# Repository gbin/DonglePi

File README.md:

DonglePi is a device that gives you a Raspberry Pi P1 compatible connector for your PC.

The RPi P1 is a defacto standard connector on all models with pins for:
- GPIO
- I2C
- SPI
- Serial
- PWM

[More info about it.](http://elinux.org/RPi_Low-level_peripherals)

On the software side, it exposes APIs that are compatible with the ones you can use on the Raspberry Pi like [GPIO](https://pypi.python.org/pypi/RPi.GPIO/) and [smbus](http://www.raspberry-projects.com/pi/programming-in-python/i2c-programming-in-python/using-the-i2c-interface-2) under python.

## Why ?

With DonglePi:
- you can use your familiar PC or Mac to directly develop & debug your RPi embedded applications (with an IDE for example)
- you can use peripherals made for the Raspberry Pi ecosystem on your PC. You can find a list of those [here](http://elinux.org/RPi_VerifiedPeripherals).

DonglePi can also be used to easily setup students for an embedded development course in a preexisting computer lab.

The fidelity with the original hardware won't be 100% but it doesn't need to be to be useful.

## Current Status

It is a prototype working on a breadboard.
The goal is to make a PCB like the one above.

On the software side:
- GPIOs are working.
- I2C is working.
- SPI is in progress.
- PWM needs to be done.
- Serial is currently used for debug but should be easy after all that :).

## Hardware

It can be plugged on any USB2 port.

You can build a prototype on a breadboard using an Atmel SAMD21 development board.
I recommend [this one](http://www.ebay.com/itm/131296219501?_trksid=p2060778.m2749.l2649&var=430589049056&ssPageName=STRK%3AMEBIDX%3AIT). Be sure to take the one with the bootloader if you are not comfortable playing with an Arm/JTAG probe.

For the RPi connector, you can use a [Pi cobbler kit](https://learn.adafruit.com/adafruit-pi-cobbler-kit/overview) from adafruit.

You can find [here](http://gbin.github.io/DonglePi/video/i2c_demo.mp4) a little demo of it driving an i2c device.

## Software

### Dependencies

Get the [asf sdk](http://www.atmel.com/System/GetBinary.ashx?target=tcm:26-49230&type=soft&actualTarget=tcm:26-65233)
It needs to be linked to the asf directory in the root of the project (by default it looks for the latest version in your home directory).

Sync the submodule:

    git submodule update --init firmware/nanopb

Install google protobuf:

    pip install -user protobuf
    #(or under arch for example)
    sudo pacman -S protobuf python2-protobuf

Install gcc for arm bare metal:

    # (under arch)
    sudo pacman -S arm-none-eabi-gcc
    # Otherwise you can always get the binaries there:
    https://launchpad.net/gcc-arm-embedded/+download

Install pyserial:

    pip install pyserial

### Building the firmware

From firmware/:

    make

It will produce a flash.bin file.

### Installing the fimware

If you have the recommanded dev board, connect it on USB, press Reset + Button B. It will appear as a standard USB storage device.
The red led from the board should slowly blink.
Copy flash.bin to the root of it.
Unmount the disk.
Reset it, the led should switch to solid red = it has correctly initialized and wait for commands.

### Building the client side support.

From python/:

    make

This should generate some files from tht protobuf so the bindings could talk to the hardware.

Here you have a test.py showing how to use the bindings.

### Debug logs.

For the moment, I have dedicated the serial output to that, you can connect it for example to a real RPi at 115200 BPS and use minicom to see the debug logs.

## Help Wanted !

Any contribution or contributor is welcomed !
If you want to contribute some code, feel free to open a pull request.
If you have some experience developing PCBs, feel free to contribute to the Eagle project.

## And the license ?

This is under CC-NY-NC 4.0 (see LICENSE.md).  
If this license doesn't fit your need: feel free to contact me at gbin@gootz.net.

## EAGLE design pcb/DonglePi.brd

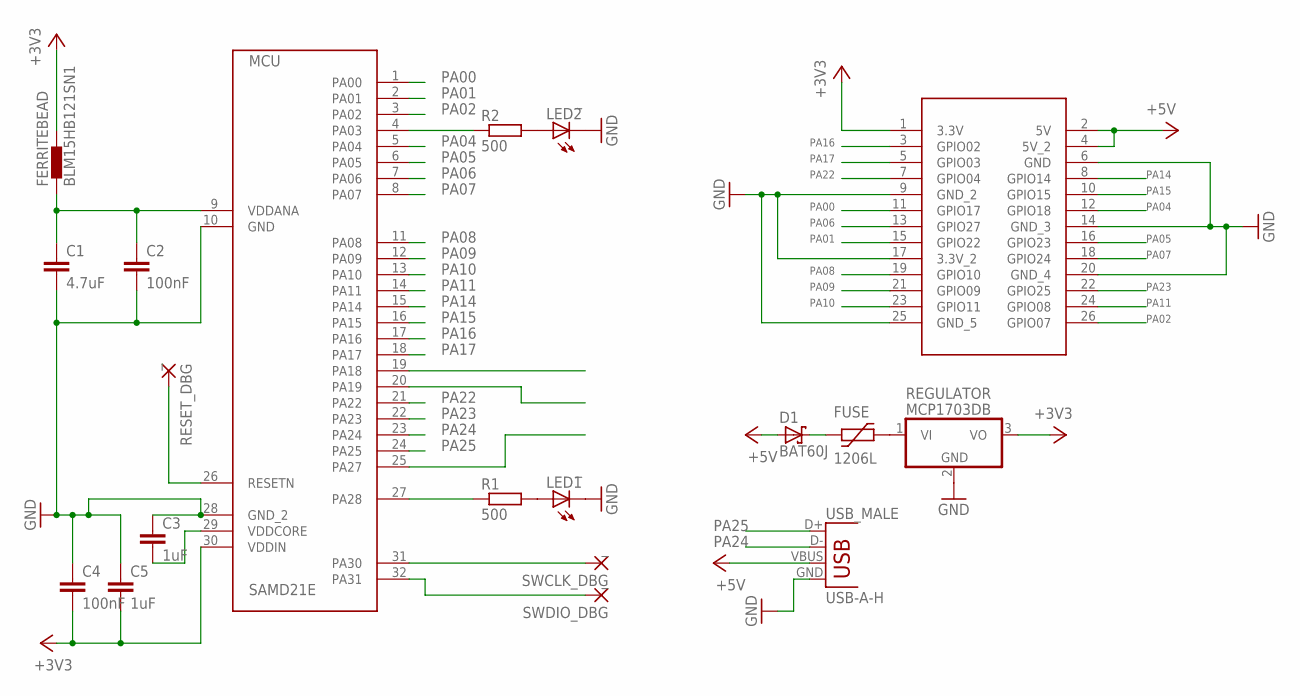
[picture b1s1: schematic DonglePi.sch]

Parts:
C1: 4.7uF; C0504
C2, C4: 100nF; C0504
C3, C5: 1uF; C0504
D1: BAT60J; SOD323_ST
FERRITEBEAD: BLM15HB121SN1; 0402
FUSE: 1206L
LED1, LED2: _; LED_SML0603
MCU: SAMD21E; TQFP32
R1, R2: 500; R0201
REGULATOR: MCP1703DB; SOT223
RESET_DBG: _; 1,6/0,8
RPIO: RPI_2X13; 2X13
SWCLK_DBG: _; 1,6/0,8
SWDIO_DBG: _; 1,6/0,8
USB_MALE: USB-A-H

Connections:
+3V3: C4.2, C5.2, FERRITEBEAD.2, MCU.30 (VDDIN), REGULATOR.3 (VO), RPIO.1 (3.3V)
+5V: D1.A, RPIO.2 (5V), RPIO.4 (5V_2), USB_MALE.VBUS
GND: C1.2, C2.2, C3.1, C4.1, C5.1, LED1.C, LED2.C, MCU.10 (GND), MCU.28 (GND_2), REGULATOR.2 (GND), RPIO.6 (GND), RPIO.9 (GND_2), RPIO.14 (GND_3), RPIO.17 (3.3V_2), RPIO.20 (GND_4), RPIO.25 (GND_5), USB_MALE.GND
unnamed: FUSE.P$2 (2), REGULATOR.1 (VI)
unnamed: D1.C, FUSE.P$1 (1)
unnamed: MCU.27 (PA28), R1.1
unnamed: LED1.A, R1.2
unnamed: C1.1, C2.1, FERRITEBEAD.1, MCU.9 (VDDANA)
unnamed: LED2.A, R2.2
unnamed: MCU.26 (RESETN), RESET_DBG.1
unnamed: C3.2, MCU.29 (VDDCORE)
PA00: MCU.1 (PA00), RPIO.11 (GPIO17)
PA01: MCU.2 (PA01), RPIO.15 (GPIO22)
PA02: MCU.3 (PA02), RPIO.26 (GPIO07)
PA03: MCU.4 (PA03), R2.1
PA04: MCU.5 (PA04), RPIO.12 (GPIO18)
PA05: MCU.6 (PA05), RPIO.16 (GPIO23)
PA06: MCU.7 (PA06), RPIO.13 (GPIO27)
PA07: MCU.8 (PA07), RPIO.18 (GPIO24)
PA08: MCU.11 (PA08), RPIO.19 (GPIO10)
PA09: MCU.12 (PA09), RPIO.21 (GPIO09)
PA10: MCU.13 (PA10), RPIO.23 (GPIO11)
PA11: MCU.14 (PA11), RPIO.24 (GPIO08)
PA14: MCU.15 (PA14), RPIO.8 (GPIO14)
PA15: MCU.16 (PA15), RPIO.10 (GPIO15)
PA16: MCU.17 (PA16), RPIO.3 (GPIO02)
PA17: MCU.18 (PA17), RPIO.5 (GPIO03)
PA18: MCU.19 (PA18)
PA19: MCU.20 (PA19)
PA22: MCU.21 (PA22), RPIO.7 (GPIO04)
PA23: MCU.22 (PA23), RPIO.22 (GPIO25)
PA24: MCU.23 (PA24), USB_MALE.D-
PA25: MCU.24 (PA25), USB_MALE.D+
PA27: MCU.25 (PA27)
PA30: MCU.31 (PA30), SWCLK_DBG.1
PA31: MCU.32 (PA31), SWDIO_DBG.1

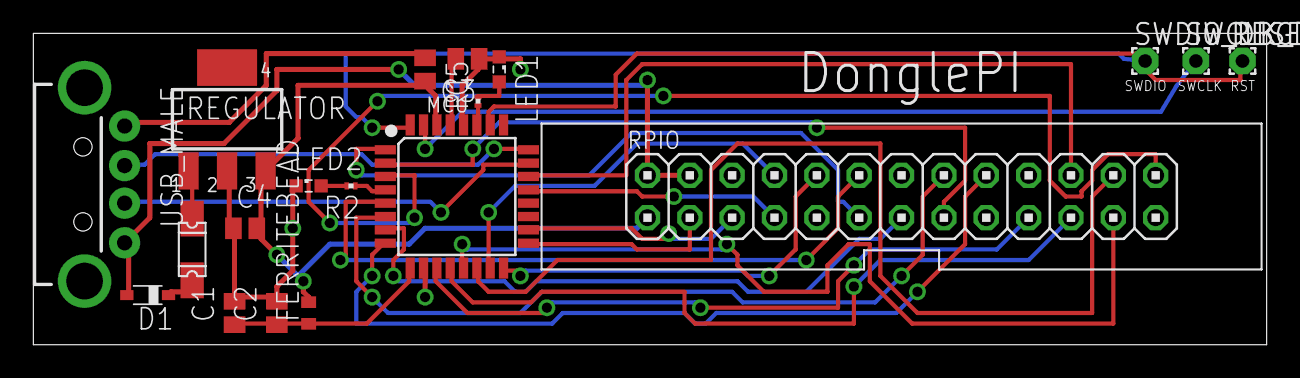
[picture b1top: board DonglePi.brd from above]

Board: 2 copper layers, 74.0 x 18.7 mm, 19 parts (0 on the bottom side), 33 nets.

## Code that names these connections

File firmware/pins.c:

#include "protocol/donglepi.pb.h"
#include "pins.h"
#include "board.h"
#include "dbg.h"

// RPI GPIO # -> SAMD pin#
uint8_t pin_map[28] = {
    0,        0,
    PIN_PA16,  // GPIO02
    PIN_PA17,  // GPIO03
    PIN_PA22,  // GPIO04
    0,        0,
    PIN_PA02,  // GPIO07
    PIN_PA11,  // GPIO08
    PIN_PA09,  // GPIO09
    PIN_PA08,  // GPIO10
    PIN_PA10,  // GPIO11
    0,        0,
    PIN_PA14,  // GPIO14
    PIN_PA15,  // GPIO15
    0,
    PIN_PA00,  // GPIO17
    PIN_PA04,  // GPIO18
    0,        0, 0,
    PIN_PA01,  // GPIO22
    PIN_PA05,  // GPIO23
    PIN_PA07,  // GPIO24
    PIN_PA23,  // GPIO25
    0,
    PIN_PA06  // GPIO27
};

static pinconfig_t pin_configs[28] = {0};

static bool i2c_on = false;
static bool uart_on = true;
static bool spi_on = false;

// returns true if the pin is assignable to a GPIO
bool is_available_for_GPIO(uint8_t pin) {
  return (pin < 28 && pin_map[pin] != 0) && !(i2c_on && is_uart_pin(pin)) &&
         !(uart_on && is_uart_pin(pin)) && !(spi_on && is_spi_pin(pin));
}

bool set_pin_GPIO_config(uint8_t pin, pinconfig_t config) {
  if (config.active && !is_available_for_GPIO(pin)) {
    return false;
  }
  pin_configs[pin] = config;
  return true;
}

bool switch_i2c(bool on) {
  if (on && (pin_configs[I2C_PIN1].active || pin_configs[I2C_PIN2].active)) {
    return false;
  }
  i2c_on = on;
  return true;
}

bool switch_spi(bool on) {
  if (on && (pin_configs[SPI_PIN1].active || pin_configs[SPI_PIN2].active ||
             pin_configs[SPI_PIN3].active || pin_configs[SPI_PIN4].active)) {
    return false;
  }
  spi_on = on;
  return true;
}

bool switch_uart(bool on) {
  if (on && (pin_configs[UART_PIN1].active || pin_configs[UART_PIN2].active)) {
    return false;
  }
#if SERIAL_DEBUG
  if (on) {
    l("ERROR: the uart is already used for the serial debug console, rebuild "
      "without SERIAL_DEBUG");
    return false;
  }
#endif
  uart_on = on;
  return true;
}

pinconfig_t* get_pin_GPIO_config(uint8_t pin) { return &(pin_configs[pin]); }

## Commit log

2014-12-30 init commit
2014-12-30 routed the mains
2014-12-30 removed backup files
2014-12-30 added gitignore
2014-12-30 Added stub for firmware
2014-12-30 added doc dir
2014-12-30 added link to xdk
2014-12-31 python doc
2014-12-31 added lz4
2014-12-31 compile test pass on lz4
2014-12-31 Better components, noise protection.
2014-12-31 pass on sch
2015-01-01 silkscreen / routing POC
2015-01-04 first uart output on A16/A17
2015-01-05 dbg + cdc working
2015-01-05 Code cleanup.
2015-01-05 added nanopb + simple proto file
2015-01-05 added Transport
2015-01-05 add the protobuf embryo in python
2015-01-06 better gitignore
2015-01-06 started to parse protobuf in the firmware
2015-01-06 starting the emulation of GPIO
2015-01-06 pass on python implementation (untested)
2015-01-07 roundtrips are working
2015-01-09 small cleanup
2015-01-10 fixed gitignore
2015-01-10 Full output implementation for GPIO.
2015-01-10 snafu gitignore
2015-01-11 Switched debug uart to PA14/15
2015-01-11 mapped I2C functions to proto
2015-01-12 initialization of i2c works.
2015-01-12 i2c pre-demo
2015-01-12 pass on uart config for the proto
2015-01-13 handles config i2c for the protocol
2015-01-13 handle various writes from python smbus (untested)
2015-01-13 moved the led display demo to python.
2015-01-13 typo
2015-01-15 refactored DonglePiRequest.Config to Config
    This is less heavy and makes some enums and structs reusable.
2015-01-16 tail for the refactor
2015-01-16 added a pin state tracker with error handling
2015-01-16 read pins now.
2015-01-17 correctly bound python GPIO IN/OUT
2015-01-17 GPIO bugs (pull ups etc.)
2015-01-17 logging
2015-01-17 remove hardcoded test
2015-01-17 better demo on the 8x8 bicolor + IN & OUT GPIO
2015-01-18 refactoring in submodule
2015-01-18 extracted the gpio module + fatal bug on gpio.values.
2015-01-22 refactoring, added missing files.
2015-01-22 correctly include nanopb extensions
2015-01-22 transformed the configs in callbacks + reorder
    This give us a better control on the decoding order.
    Now the configs will be called before the data which can depend on.
2015-01-22 cleanup the usb/uart blougiboulga
    (those were zombies from the initial example)
2015-01-22 remove unused LPM code
2015-01-22 introduced SERIAL_DEBUG compilation variable.
2015-01-22 removed redundant boolean check for i2c
2015-01-22 don't declare unused variables in non SERIAL_DEBUG
2015-01-22 refuse to enable the usart if we are in SERIAL_DEBUG
2015-01-22 implementation of handling of uart config
2015-01-25 Fixed the python example
2015-01-26 added spi hardcoded example
2015-01-27 general code reformat
2015-01-29 pass on making the build easier
2015-01-29 reorg for building
2015-01-29 now compiles with new asf / new toolchain
2015-01-31 more temp instructions for python stuff
2015-01-31 moved spi stuff in own file.
2015-02-05 Reorganized the boot sequence
2015-02-05 added openocd config
2015-02-05 added a simple tool to copy flash
2015-02-05 make it compile with spi dummy code.
2015-02-17 pass on spi (enable message works).
    Still no clock though
2015-02-17 stop the test for SPI diagnosis.
2015-02-17 hardcode the dongle pi as it doesn't advertise anymore
2015-02-22 Added the SPI interface to the proto.
2015-02-22 Pass on README.md
2015-02-22 pass on README
2015-02-22 title
2015-02-22 Create gh-pages branch via GitHub
2015-02-22 images
2015-02-22 pcb url
2015-02-22 added the pres as main page
2015-02-22 pass on html
2015-02-22 removed section
2015-02-22 pass on readme license
2015-02-23 added license
2015-02-23 added docs
2015-02-23 added fixed formatting
2015-02-23 added an i2c demo
2015-02-23 embed the video demo
2015-02-23 put the video as link
2015-02-23 better codeblocks
2015-02-23 another codeblock
2015-02-23 forgot serial in the todo list
2015-02-25 added , renamed ods fil
2015-02-25 add mapping-donglepi-rpi.pdf
2015-02-25 add PNGs
2015-02-25 better PDF orientation
2015-02-26 New License
